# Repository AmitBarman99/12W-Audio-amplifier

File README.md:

# 12W-Audio-amplifier

An audio amplifier of power gain 12W

### The 3D photo

> I used kiCAD for circuit and pcb design

**Don't forget to show your love by giving a 🌟 to this repository**

~ Designed by Amit Barman<br>
[Website](https://abhisandhi.netlify.app)<br>
[LinkedIn](https://www.linkedin.com/in/amitbarman99)<br>
[GitHub](https://github.com/Amitbarman99)<br>
[Twitter](https://twitter.com/imamitbarman99)

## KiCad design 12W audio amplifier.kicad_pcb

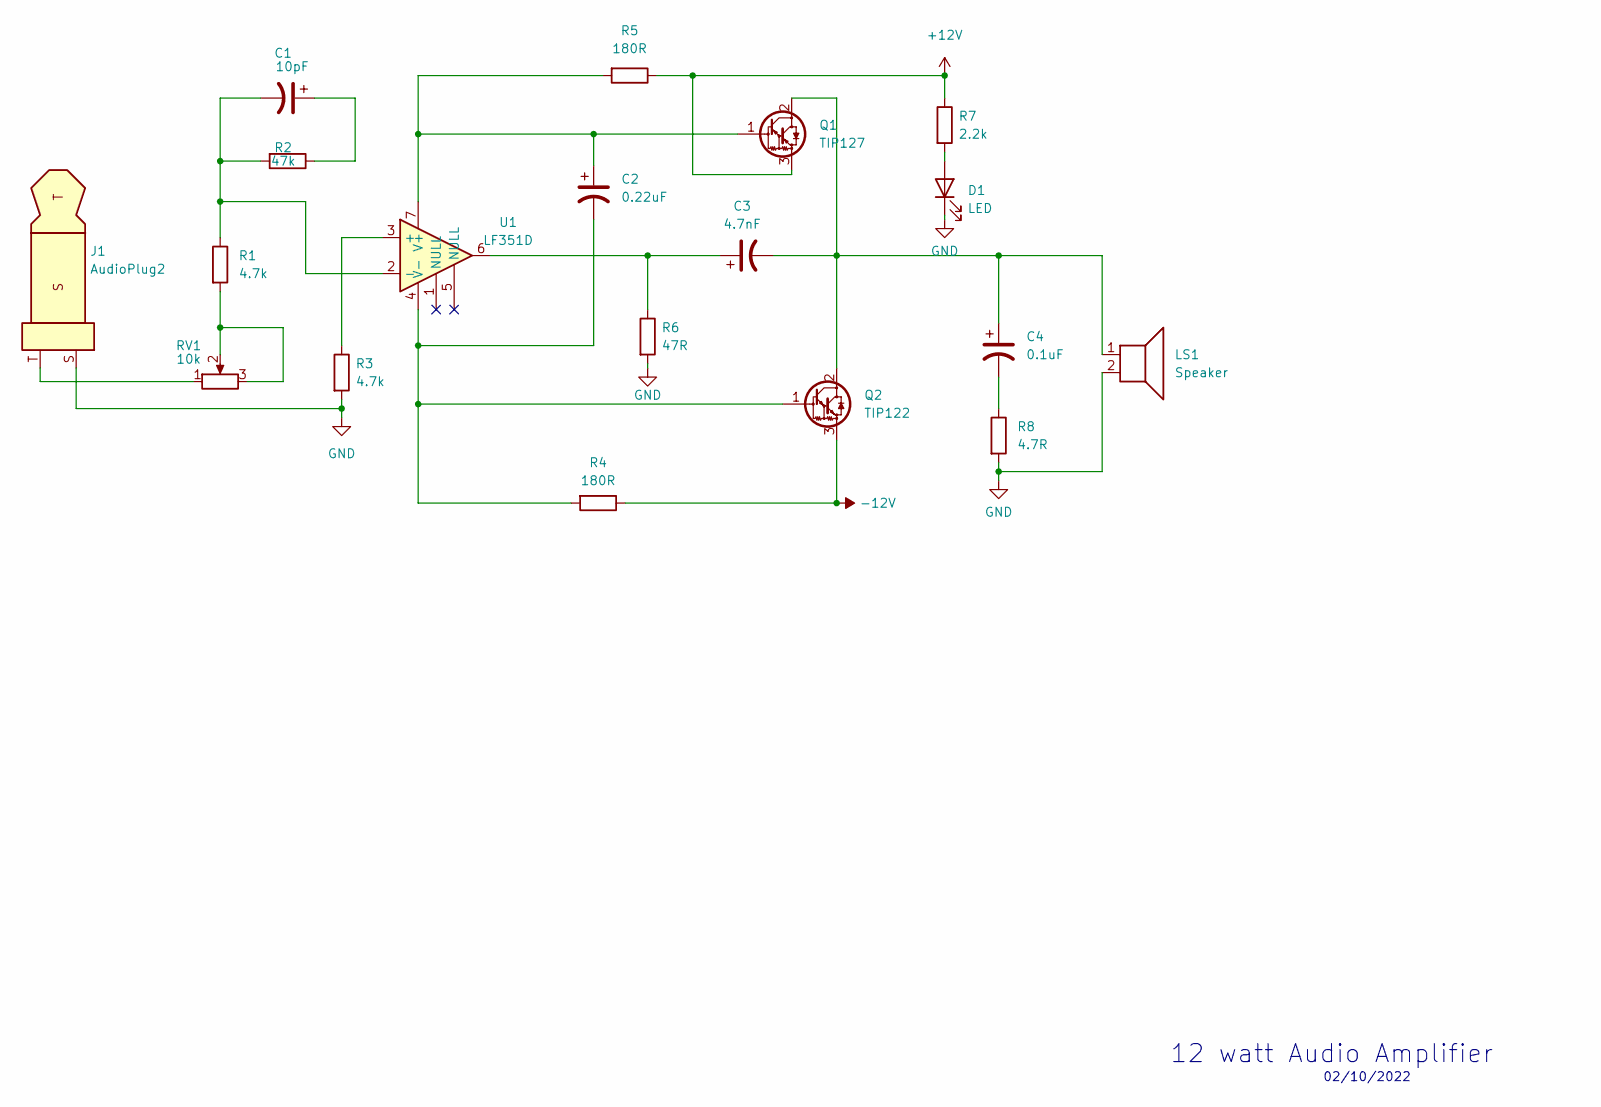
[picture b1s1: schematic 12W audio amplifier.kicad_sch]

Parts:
C1: 10pF; CP_Elec_3x5.3
C2: 0.22uF; CP_Elec_3x5.3
C3: 4.7nF; CP_Elec_3x5.3
C4: 0.1uF; CP_Elec_3x5.3
D1: LED; LED_0201_0603Metric
J1: AudioPlug2
LS1: Speaker; PinHeader_1x02_P1.27mm_Vertical
Q1: TIP127; TO-220-3_Vertical
Q2: TIP122; TO-220-3_Vertical
R1, R3: 4.7k; R_0201_0603Metric
R2: 47k; R_0201_0603Metric
R4, R5: 180R; R_0201_0603Metric
R6: 47R; R_0201_0603Metric
R7: 2.2k; R_0201_0603Metric
R8: 4.7R; R_0201_0603Metric
RV1: 10k; Potentiometer_ACP_CA6-VSMD_Vertical
U1: LF351D; SOIC-8_3.9x4.9mm_P1.27mm

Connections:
+12V: Q1.3 (E), R5.1, R7.1
-12V: Q2.3 (E), R4.1
GND: D1.1 (K), J1.S, LS1.2, R3.2, R6.2, R8.2
unnamed: C1.1, R2.1
unnamed: C1.2, R1.1, R2.2, U1.2 (-)
unnamed: C2.1, Q1.1 (B), R5.2, U1.7 (V+)
unnamed: C2.2, Q2.1 (B), R4.2, U1.4 (V-)
unnamed: C3.1, R6.1, U1.6
unnamed: C3.2, C4.1, LS1.1, Q1.2 (C), Q2.2 (C)
unnamed: C4.2, R8.1
unnamed: D1.2 (A), R7.2
unnamed: J1.T, RV1.1
unnamed: R1.2, RV1.2, RV1.3
unnamed: R3.1, U1.3 (+)

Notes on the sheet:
02/10/2022
12 watt Audio Amplifier

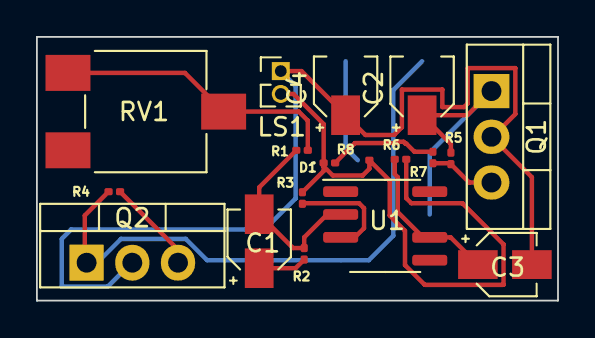
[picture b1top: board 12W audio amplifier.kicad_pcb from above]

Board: 2 copper layers, 29.0 x 14.7 mm, 18 parts (0 on the bottom side), 13 nets.

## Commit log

2022-10-01 Initial commit
    create file,completed schemetic design
2022-10-02 updated schematic diagram
    annotations,footprints setup
2022-10-03 added pcb design file
2022-10-03 added the preview image
2022-10-05 added schematic circuit pdf
    the circuit diagram
2022-10-05 added pcb layout
2022-10-05 added 3D design file
    3d .wrl file of the board
